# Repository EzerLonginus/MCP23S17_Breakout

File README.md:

# MCP23S17_Breakout
Breakout for MCP23S17

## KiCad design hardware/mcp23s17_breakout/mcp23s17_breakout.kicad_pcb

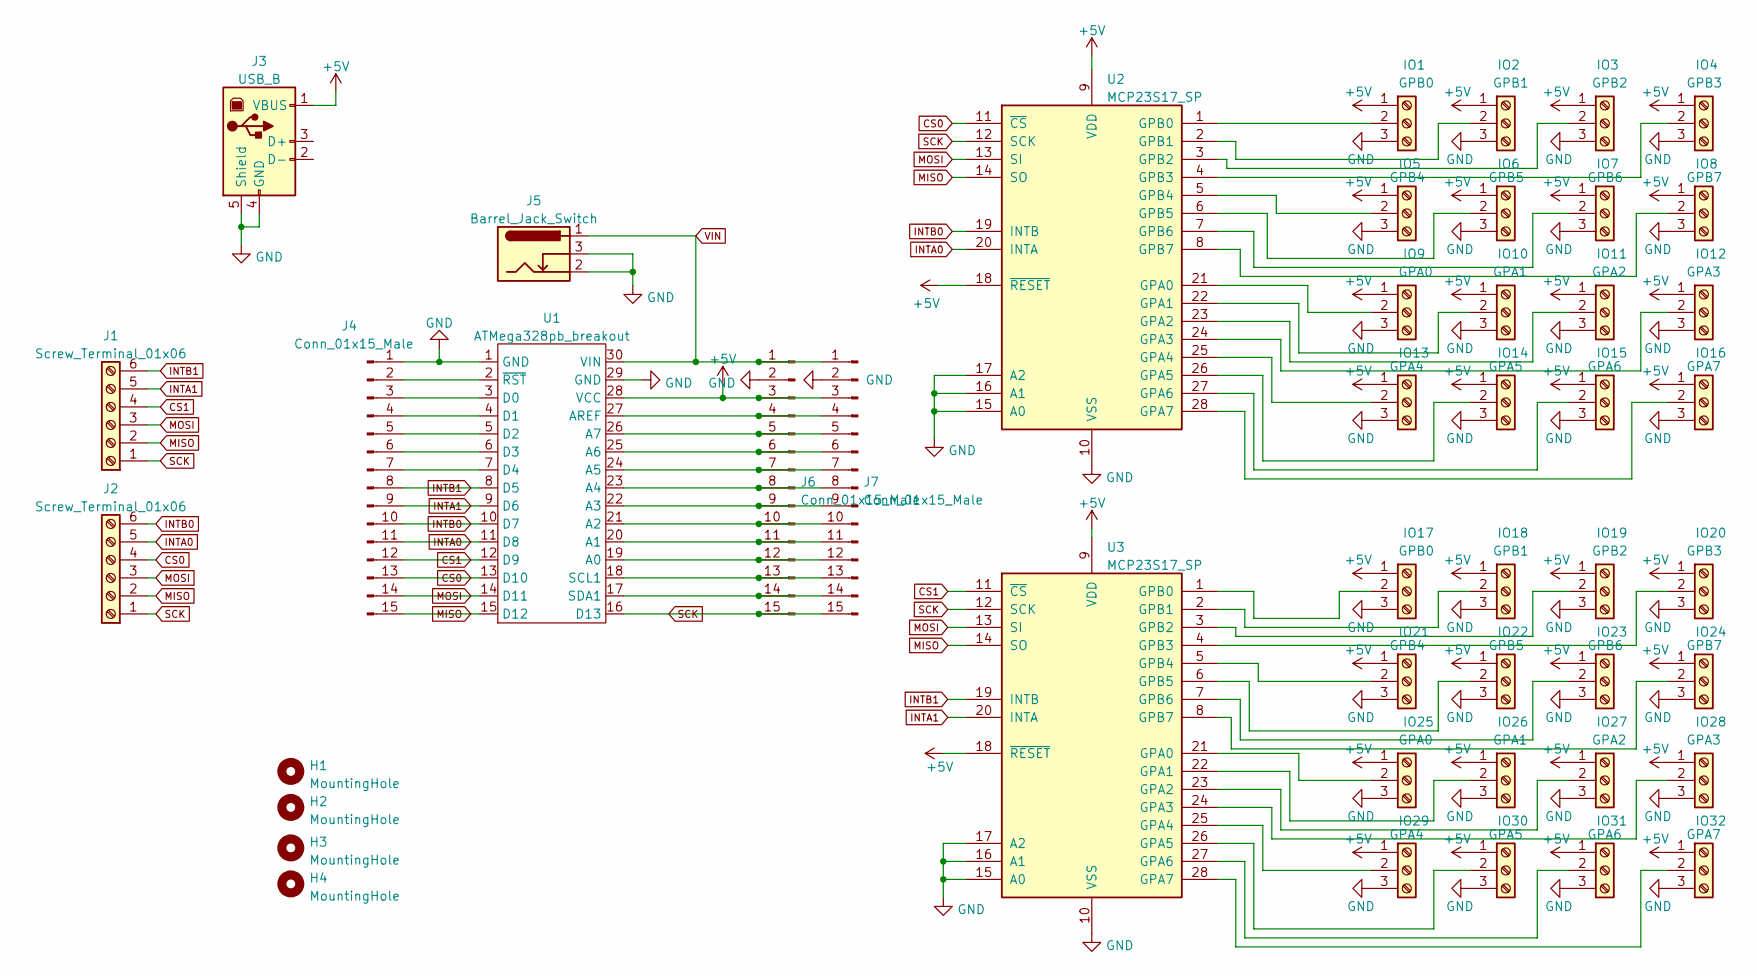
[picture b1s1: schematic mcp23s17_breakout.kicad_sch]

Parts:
H1, H2, H3, H4: MountingHole; MountingHole_3.2mm_M3_DIN965_Pad
IO1, IO17: GPB0; TerminalBlock_TE_282834-3_1x03_P2.54mm_Horizontal
IO2, IO18: GPB1; TerminalBlock_TE_282834-3_1x03_P2.54mm_Horizontal
IO3, IO19: GPB2; TerminalBlock_TE_282834-3_1x03_P2.54mm_Horizontal
IO4, IO20: GPB3; TerminalBlock_TE_282834-3_1x03_P2.54mm_Horizontal
IO5, IO21: GPB4; TerminalBlock_TE_282834-3_1x03_P2.54mm_Horizontal
IO6, IO22: GPB5; TerminalBlock_TE_282834-3_1x03_P2.54mm_Horizontal
IO7, IO23: GPB6; TerminalBlock_TE_282834-3_1x03_P2.54mm_Horizontal
IO8, IO24: GPB7; TerminalBlock_TE_282834-3_1x03_P2.54mm_Horizontal
IO9, IO25: GPA0; TerminalBlock_TE_282834-3_1x03_P2.54mm_Horizontal
IO10, IO26: GPA1; TerminalBlock_TE_282834-3_1x03_P2.54mm_Horizontal
IO11, IO27: GPA2; TerminalBlock_TE_282834-3_1x03_P2.54mm_Horizontal
IO12, IO28: GPA3; TerminalBlock_TE_282834-3_1x03_P2.54mm_Horizontal
IO13, IO29: GPA4; TerminalBlock_TE_282834-3_1x03_P2.54mm_Horizontal
IO14, IO30: GPA5; TerminalBlock_TE_282834-3_1x03_P2.54mm_Horizontal
IO15, IO31: GPA6; TerminalBlock_TE_282834-3_1x03_P2.54mm_Horizontal
IO16, IO32: GPA7; TerminalBlock_TE_282834-3_1x03_P2.54mm_Horizontal
J1, J2: Screw_Terminal_01x06; TerminalBlock_TE_282834-6_1x06_P2.54mm_Horizontal
J3: USB_B; USB_B_Lumberg_2411_02_Horizontal
J4, J6, J7: Conn_01x15_Male; PinHeader_1x15_P2.54mm_Vertical
J5: Barrel_Jack_Switch; BarrelJack_GCT_DCJ200-10-A_Horizontal
U1: ATMega328pb_breakout
U2, U3: MCP23S17_SP; DIP-28_W7.62mm

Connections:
+5V: IO1.1, IO2.1, IO3.1, IO4.1, IO5.1, IO6.1, IO7.1, IO8.1, IO9.1, IO10.1, IO11.1, IO12.1, IO13.1, IO14.1, IO15.1, IO16.1, IO17.1, IO18.1, IO19.1, IO20.1, IO21.1, IO22.1, IO23.1, IO24.1, IO25.1, IO26.1, IO27.1, IO28.1, IO29.1, IO30.1, IO31.1, IO32.1, J3.1 (VBUS), J6.3, J7.3, U1.28 (VCC), U2.9 (VDD), U2.18 (~RESET), U3.9 (VDD), U3.18 (~RESET)
CS0: J2.4, J4.13, U1.13 (D10), U2.11 (~CS)
CS1: J1.4, J4.12, U1.12 (D9), U3.11 (~CS)
GND: IO1.3, IO2.3, IO3.3, IO4.3, IO5.3, IO6.3, IO7.3, IO8.3, IO9.3, IO10.3, IO11.3, IO12.3, IO13.3, IO14.3, IO15.3, IO16.3, IO17.3, IO18.3, IO19.3, IO20.3, IO21.3, IO22.3, IO23.3, IO24.3, IO25.3, IO26.3, IO27.3, IO28.3, IO29.3, IO30.3, IO31.3, IO32.3, J3.4 (GND), J3.5 (Shield), J4.1, J5.2, J5.3, J6.2, J7.2, U1.1 (GND), U1.29 (GND), U2.10 (VSS), U2.15 (A0), U2.16 (A1), U2.17 (A2), U3.10 (VSS), U3.15 (A0), U3.16 (A1), U3.17 (A2)
INTA0: J2.5, J4.11, U1.11 (D8), U2.20 (INTA)
INTA1: J1.5, J4.9, U1.9 (D6), U3.20 (INTA)
INTB0: J2.6, J4.10, U1.10 (D7), U2.19 (INTB)
INTB1: J1.6, J4.8, U1.8 (D5), U3.19 (INTB)
MISO: J1.2, J2.2, J4.15, U1.15 (D12), U2.14 (SO), U3.14 (SO)
MOSI: J1.3, J2.3, J4.14, U1.14 (D11), U2.13 (SI), U3.13 (SI)
unnamed: IO1.2, U2.1 (GPB0)
unnamed: IO2.2, U2.2 (GPB1)
unnamed: IO3.2, U2.3 (GPB2)
unnamed: IO4.2, U2.4 (GPB3)
unnamed: IO5.2, U2.5 (GPB4)
unnamed: IO6.2, U2.6 (GPB5)
unnamed: IO7.2, U2.7 (GPB6)
unnamed: IO8.2, U2.8 (GPB7)
unnamed: IO9.2, U2.21 (GPA0)
unnamed: IO10.2, U2.22 (GPA1)
unnamed: IO11.2, U2.23 (GPA2)
unnamed: IO12.2, U2.24 (GPA3)
unnamed: IO13.2, U2.25 (GPA4)
unnamed: IO14.2, U2.26 (GPA5)
unnamed: IO15.2, U2.27 (GPA6)
unnamed: IO16.2, U2.28 (GPA7)
unnamed: IO17.2, U3.1 (GPB0)
unnamed: IO18.2, U3.2 (GPB1)
unnamed: IO19.2, U3.3 (GPB2)
unnamed: IO20.2, U3.4 (GPB3)
unnamed: IO21.2, U3.5 (GPB4)
unnamed: IO22.2, U3.6 (GPB5)
unnamed: IO23.2, U3.7 (GPB6)
unnamed: IO24.2, U3.8 (GPB7)
unnamed: IO25.2, U3.21 (GPA0)
unnamed: IO26.2, U3.22 (GPA1)
unnamed: IO27.2, U3.23 (GPA2)
unnamed: IO28.2, U3.24 (GPA3)
unnamed: IO29.2, U3.25 (GPA4)
unnamed: IO30.2, U3.26 (GPA5)
unnamed: IO31.2, U3.27 (GPA6)
unnamed: IO32.2, U3.28 (GPA7)
unnamed: J4.2, U1.2 (~RST)
unnamed: J4.3, U1.3 (D0)
unnamed: J4.4, U1.4 (D1)
unnamed: J4.5, U1.5 (D2)
unnamed: J4.6, U1.6 (D3)
unnamed: J4.7, U1.7 (D4)
unnamed: J6.4, J7.4, U1.27 (AREF)
unnamed: J6.5, J7.5, U1.26 (A7)
unnamed: J6.6, J7.6, U1.25 (A6)
unnamed: J6.7, J7.7, U1.24 (A5)
unnamed: J6.8, J7.8, U1.23 (A4)
unnamed: J6.9, J7.9, U1.22 (A3)
unnamed: J6.10, J7.10, U1.21 (A2)
unnamed: J6.11, J7.11, U1.20 (A1)
unnamed: J6.12, J7.12, U1.19 (A0)
unnamed: J6.13, J7.13, U1.18 (SCL1)
unnamed: J6.14, J7.14, U1.17 (SDA1)
SCK: J1.1, J2.1, J6.15, J7.15, U1.16 (D13), U2.12 (SCK), U3.12 (SCK)
VIN: J5.1, J6.1, J7.1, U1.30 (VIN)

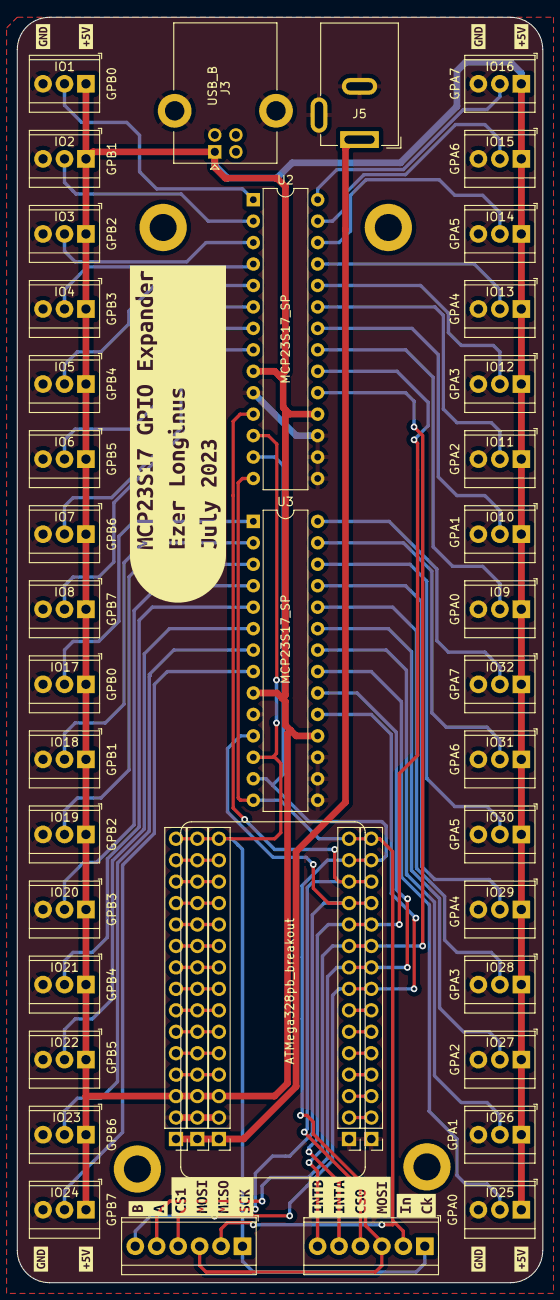
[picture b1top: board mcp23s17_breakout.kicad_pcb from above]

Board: 2 copper layers, 62.2 x 149.9 mm, 59 parts (0 on the bottom side), 61 nets.

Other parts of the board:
kibuzzard-64B054A6, kibuzzard-64B054A6#2, kibuzzard-64B054A6#3: G***; kibuzzard-64B054A6
kibuzzard-64B056E4: G***; kibuzzard-64B056E4
kibuzzard-64B0570E: G***; kibuzzard-64B0570E
kibuzzard-64B0572C: G***; kibuzzard-64B0572C
kibuzzard-64B0577B: G***; kibuzzard-64B0577B
kibuzzard-64B05466: G***; kibuzzard-64B05466
kibuzzard-64B05493, kibuzzard-64B05493#2, kibuzzard-64B05493#3, kibuzzard-64B05493#4: G***; kibuzzard-64B05493
kibuzzard-64B05998: G***; kibuzzard-64B05998

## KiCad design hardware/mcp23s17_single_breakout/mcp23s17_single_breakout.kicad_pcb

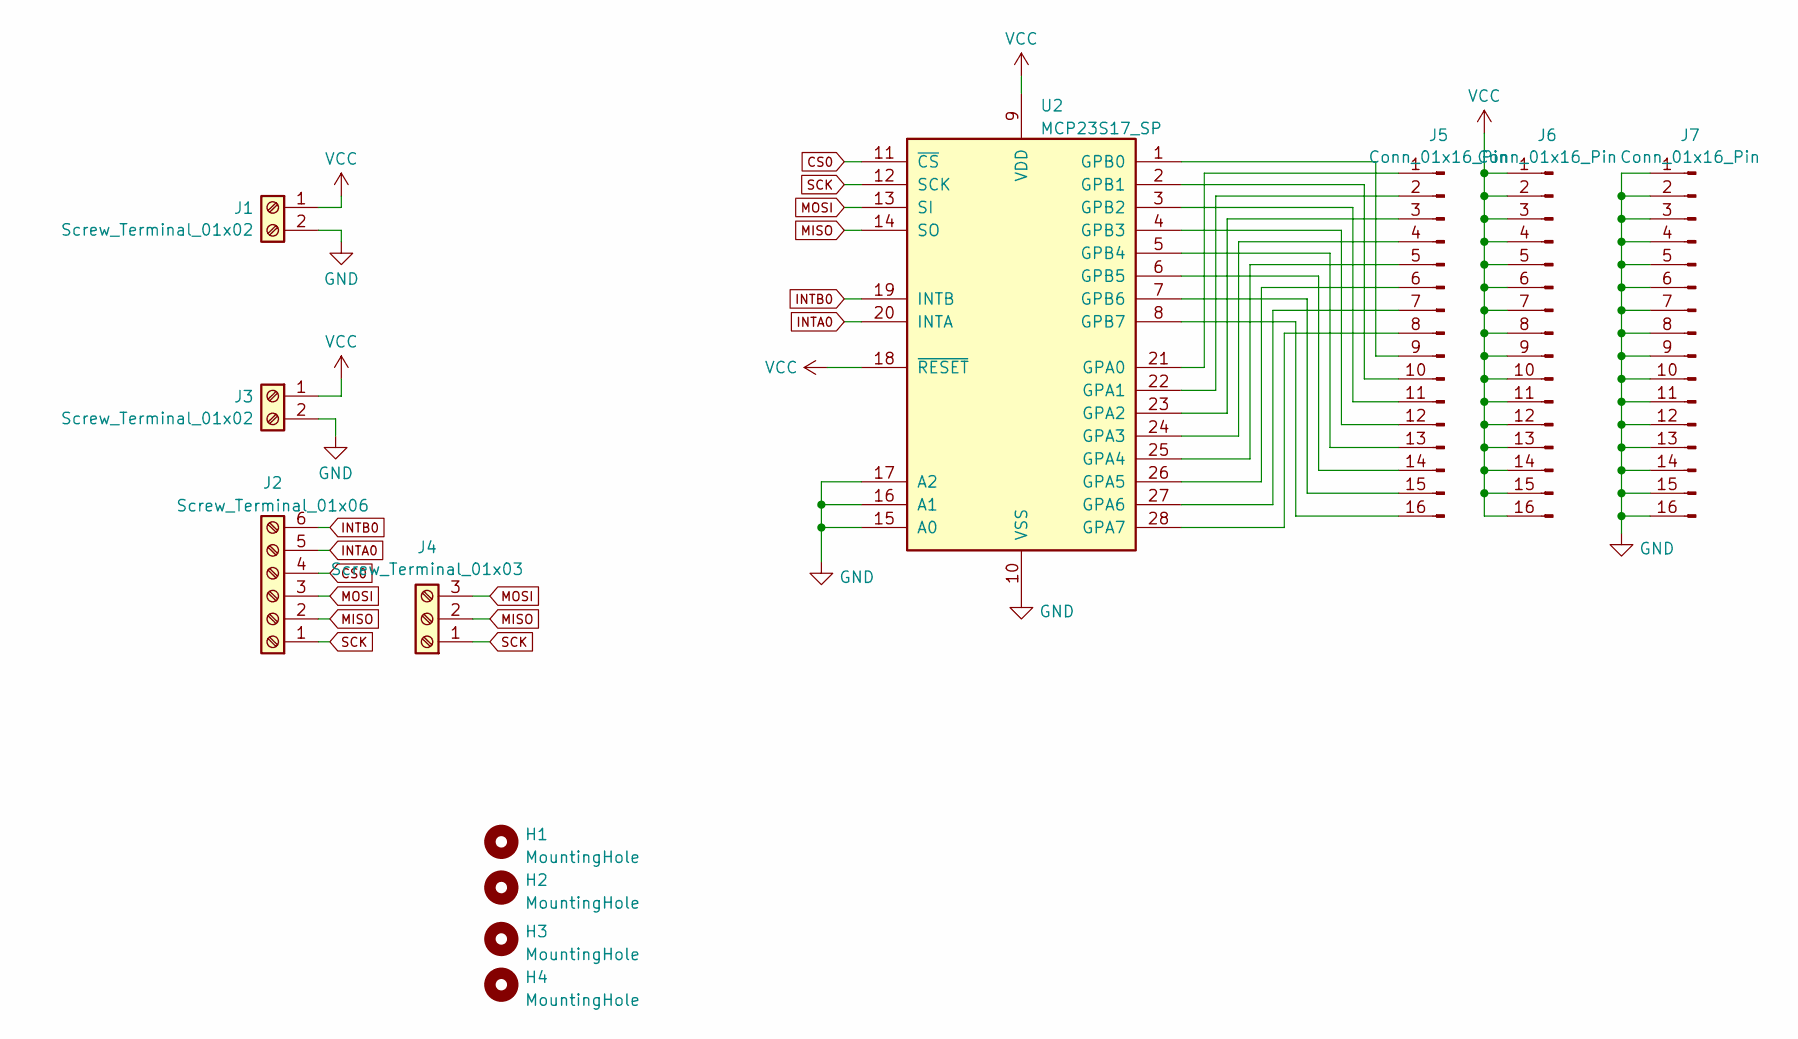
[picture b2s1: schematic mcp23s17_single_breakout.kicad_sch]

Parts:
H1, H2, H3, H4: MountingHole; MountingHole_3.2mm_M3_DIN965_Pad
J1, J3: Screw_Terminal_01x02; TerminalBlock_bornier-2_P5.08mm
J2: Screw_Terminal_01x06; TerminalBlock_4Ucon_1x06_P3.50mm_Horizontal
J4: Screw_Terminal_01x03; TerminalBlock_4Ucon_1x03_P3.50mm_Horizontal
J5, J6, J7: Conn_01x16_Pin; PinHeader_1x16_P2.54mm_Vertical
U2: MCP23S17_SP; DIP-28_W7.62mm

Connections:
CS0: J2.4, U2.11 (~CS)
GND: J1.2, J3.2, J7.1, J7.2, J7.3, J7.4, J7.5, J7.6, J7.7, J7.8, J7.9, J7.10, J7.11, J7.12, J7.13, J7.14, J7.15, J7.16, U2.10 (VSS), U2.15 (A0), U2.16 (A1), U2.17 (A2)
INTA0: J2.5, U2.20 (INTA)
INTB0: J2.6, U2.19 (INTB)
MISO: J2.2, J4.2, U2.14 (SO)
MOSI: J2.3, J4.3, U2.13 (SI)
unnamed: J5.1, U2.21 (GPA0)
unnamed: J5.2, U2.22 (GPA1)
unnamed: J5.3, U2.23 (GPA2)
unnamed: J5.4, U2.24 (GPA3)
unnamed: J5.5, U2.25 (GPA4)
unnamed: J5.6, U2.26 (GPA5)
unnamed: J5.7, U2.27 (GPA6)
unnamed: J5.8, U2.28 (GPA7)
unnamed: J5.9, U2.1 (GPB0)
unnamed: J5.10, U2.2 (GPB1)
unnamed: J5.11, U2.3 (GPB2)
unnamed: J5.12, U2.4 (GPB3)
unnamed: J5.13, U2.5 (GPB4)
unnamed: J5.14, U2.6 (GPB5)
unnamed: J5.15, U2.7 (GPB6)
unnamed: J5.16, U2.8 (GPB7)
SCK: J2.1, J4.1, U2.12 (SCK)
VCC: J1.1, J3.1, J6.1, J6.2, J6.3, J6.4, J6.5, J6.6, J6.7, J6.8, J6.9, J6.10, J6.11, J6.12, J6.13, J6.14, J6.15, J6.16, U2.9 (VDD), U2.18 (~RESET)

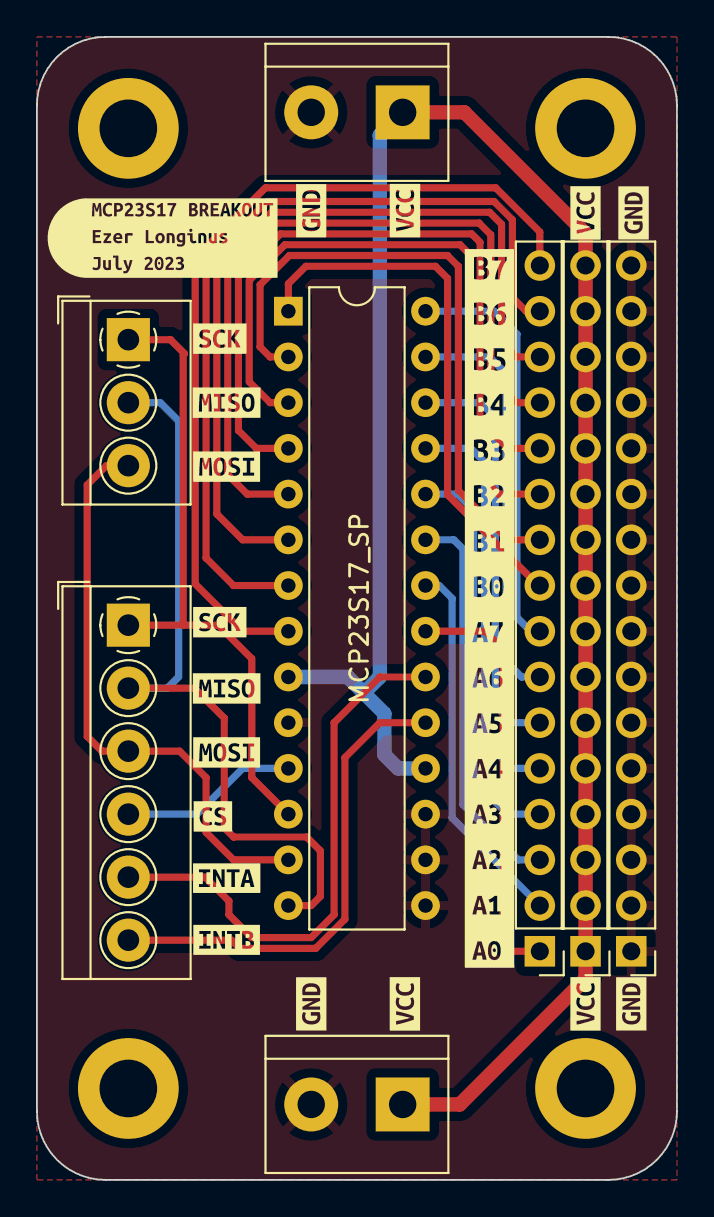
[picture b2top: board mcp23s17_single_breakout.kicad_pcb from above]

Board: 2 copper layers, 35.6 x 63.5 mm, 31 parts (0 on the bottom side), 24 nets.

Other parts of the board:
kibuzzard-64B17B8E, kibuzzard-64B17B8E#2: G***; kibuzzard-64B17B8E
kibuzzard-64B17BBB, kibuzzard-64B17BBB#2: G***; kibuzzard-64B17BBB
kibuzzard-64B17BDD, kibuzzard-64B17BDD#2: G***; kibuzzard-64B17BDD
kibuzzard-64B17C16: G***; kibuzzard-64B17C16
kibuzzard-64B17C26: G***; kibuzzard-64B17C26
kibuzzard-64B17C33: G***; kibuzzard-64B17C33
kibuzzard-64B17C58, kibuzzard-64B17C58#2, kibuzzard-64B17C58#3, kibuzzard-64B17C58#4: G***; kibuzzard-64B17C58
kibuzzard-64B17C80, kibuzzard-64B17C80#2, kibuzzard-64B17C80#3, kibuzzard-64B17C80#4: G***; kibuzzard-64B17C80
kibuzzard-64B17E8C: G***; kibuzzard-64B17E8C
kibuzzard-64B56916: G***; kibuzzard-64B56916

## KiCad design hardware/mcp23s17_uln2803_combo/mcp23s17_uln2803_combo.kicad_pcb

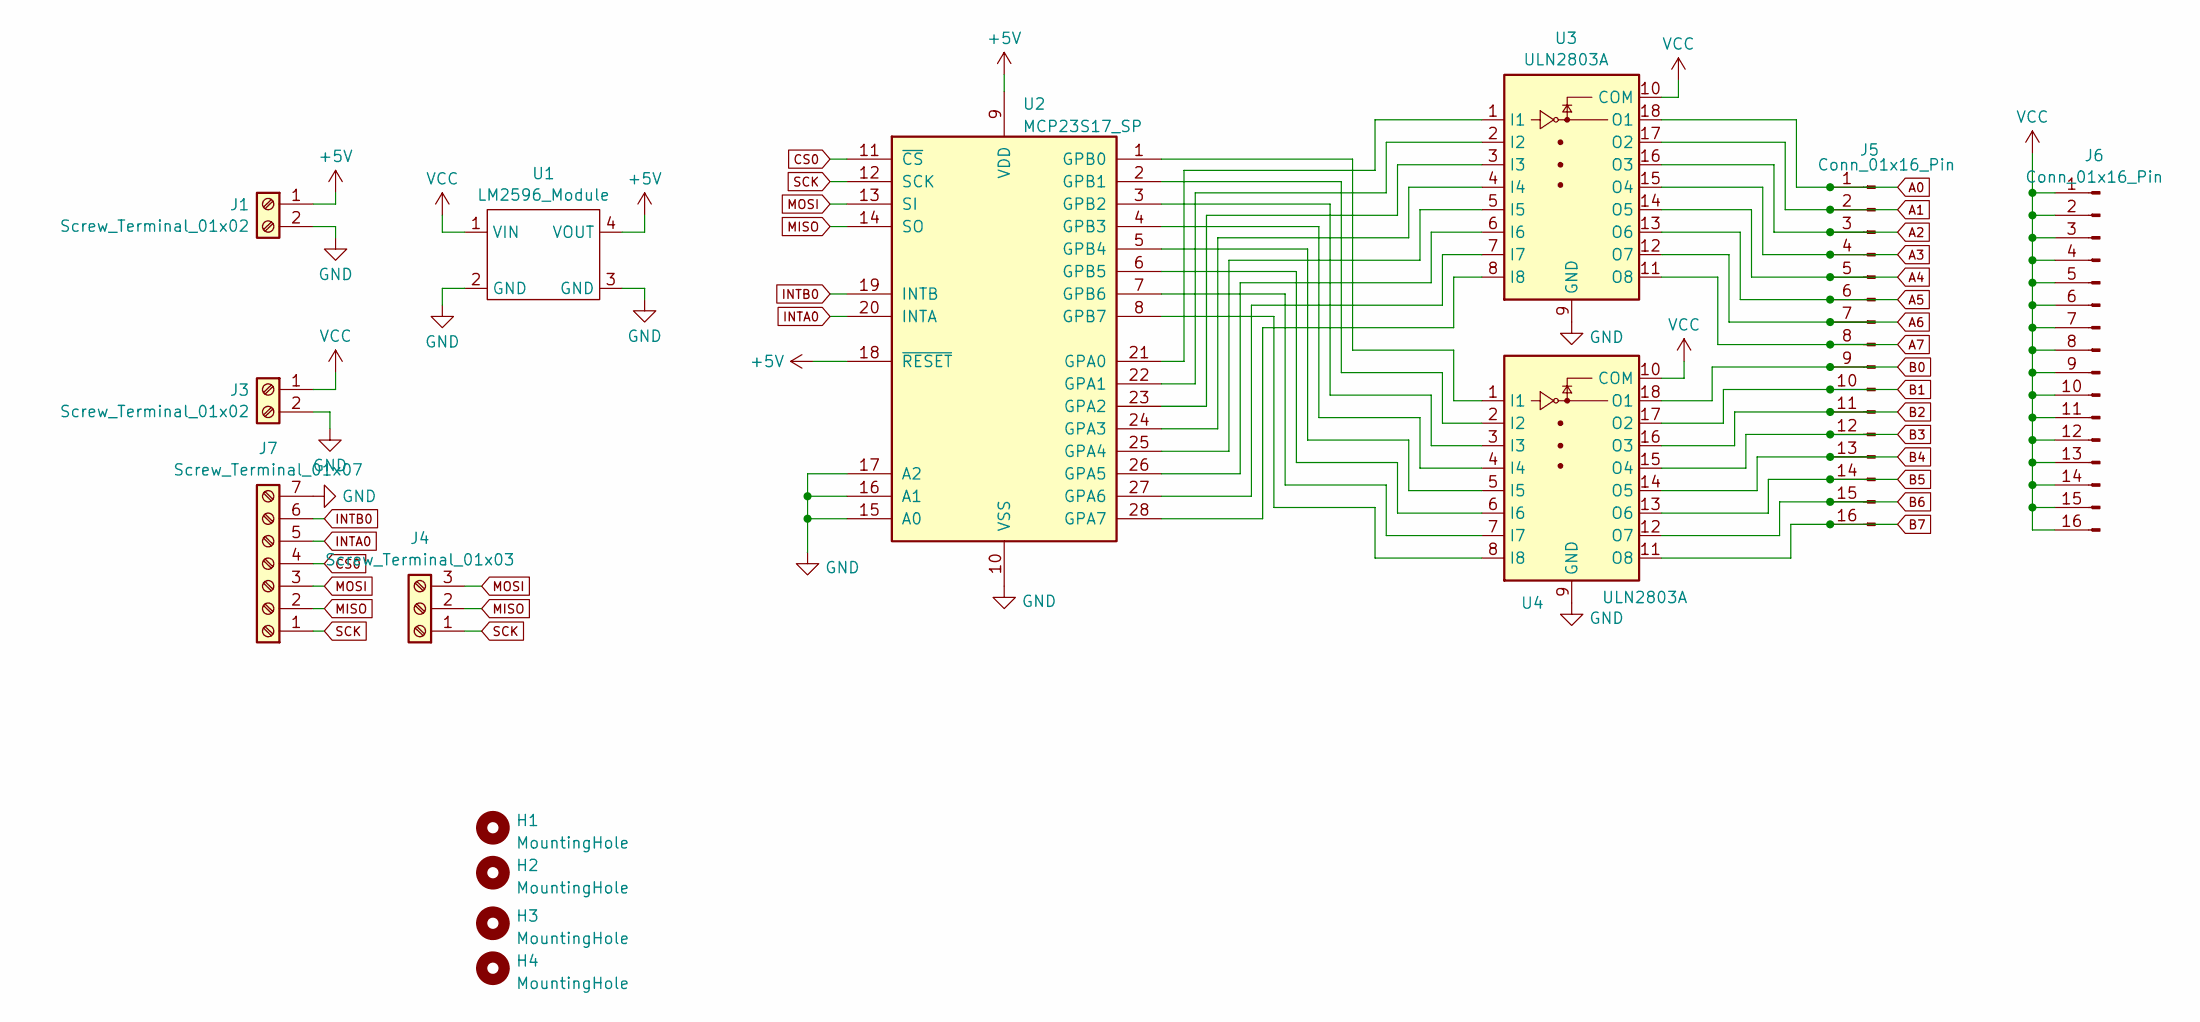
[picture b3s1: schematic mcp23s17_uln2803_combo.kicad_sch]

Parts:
H1, H2, H3, H4: MountingHole; MountingHole_3.2mm_M3_DIN965_Pad
J1, J3: Screw_Terminal_01x02; TerminalBlock_bornier-2_P5.08mm
J4: Screw_Terminal_01x03; TerminalBlock_4Ucon_1x03_P3.50mm_Horizontal
J5, J6: Conn_01x16_Pin; PinHeader_1x16_P2.54mm_Vertical
J7: Screw_Terminal_01x07; TerminalBlock_4Ucon_1x07_P3.50mm_Horizontal
U1: LM2596_Module; LM2596_StepDown_Module
U2: MCP23S17_SP; DIP-28_W7.62mm
U3, U4: ULN2803A; DIP-18_W7.62mm_LongPads

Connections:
+5V: J1.1, U1.4 (VOUT), U2.9 (VDD), U2.18 (~RESET)
A0: J5.1, U3.18 (O1)
A1: J5.2, U3.17 (O2)
A2: J5.3, U3.16 (O3)
A3: J5.4, U3.15 (O4)
A4: J5.5, U3.14 (O5)
A5: J5.6, U3.13 (O6)
A6: J5.7, U3.12 (O7)
A7: J5.8, U3.11 (O8)
B0: J5.9, U4.18 (O1)
B1: J5.10, U4.17 (O2)
B2: J5.11, U4.16 (O3)
B3: J5.12, U4.15 (O4)
B4: J5.13, U4.14 (O5)
B5: J5.14, U4.13 (O6)
B6: J5.15, U4.12 (O7)
B7: J5.16, U4.11 (O8)
CS0: J7.4, U2.11 (~CS)
GND: J1.2, J3.2, J7.7, U1.2 (GND), U1.3 (GND), U2.10 (VSS), U2.15 (A0), U2.16 (A1), U2.17 (A2), U3.9 (GND), U4.9 (GND)
INTA0: J7.5, U2.20 (INTA)
INTB0: J7.6, U2.19 (INTB)
MISO: J4.2, J7.2, U2.14 (SO)
MOSI: J4.3, J7.3, U2.13 (SI)
unnamed: U2.21 (GPA0), U3.1 (I1)
unnamed: U2.22 (GPA1), U3.2 (I2)
unnamed: U2.23 (GPA2), U3.3 (I3)
unnamed: U2.24 (GPA3), U3.4 (I4)
unnamed: U2.25 (GPA4), U3.5 (I5)
unnamed: U2.26 (GPA5), U3.6 (I6)
unnamed: U2.27 (GPA6), U3.7 (I7)
unnamed: U2.28 (GPA7), U3.8 (I8)
unnamed: U2.1 (GPB0), U4.1 (I1)
unnamed: U2.2 (GPB1), U4.2 (I2)
unnamed: U2.3 (GPB2), U4.3 (I3)
unnamed: U2.4 (GPB3), U4.4 (I4)
unnamed: U2.5 (GPB4), U4.5 (I5)
unnamed: U2.6 (GPB5), U4.6 (I6)
unnamed: U2.7 (GPB6), U4.7 (I7)
unnamed: U2.8 (GPB7), U4.8 (I8)
SCK: J4.1, J7.1, U2.12 (SCK)
VCC: J3.1, J6.1, J6.2, J6.3, J6.4, J6.5, J6.6, J6.7, J6.8, J6.9, J6.10, J6.11, J6.12, J6.13, J6.14, J6.15, J6.16, U1.1 (VIN), U3.10 (COM), U4.10 (COM)

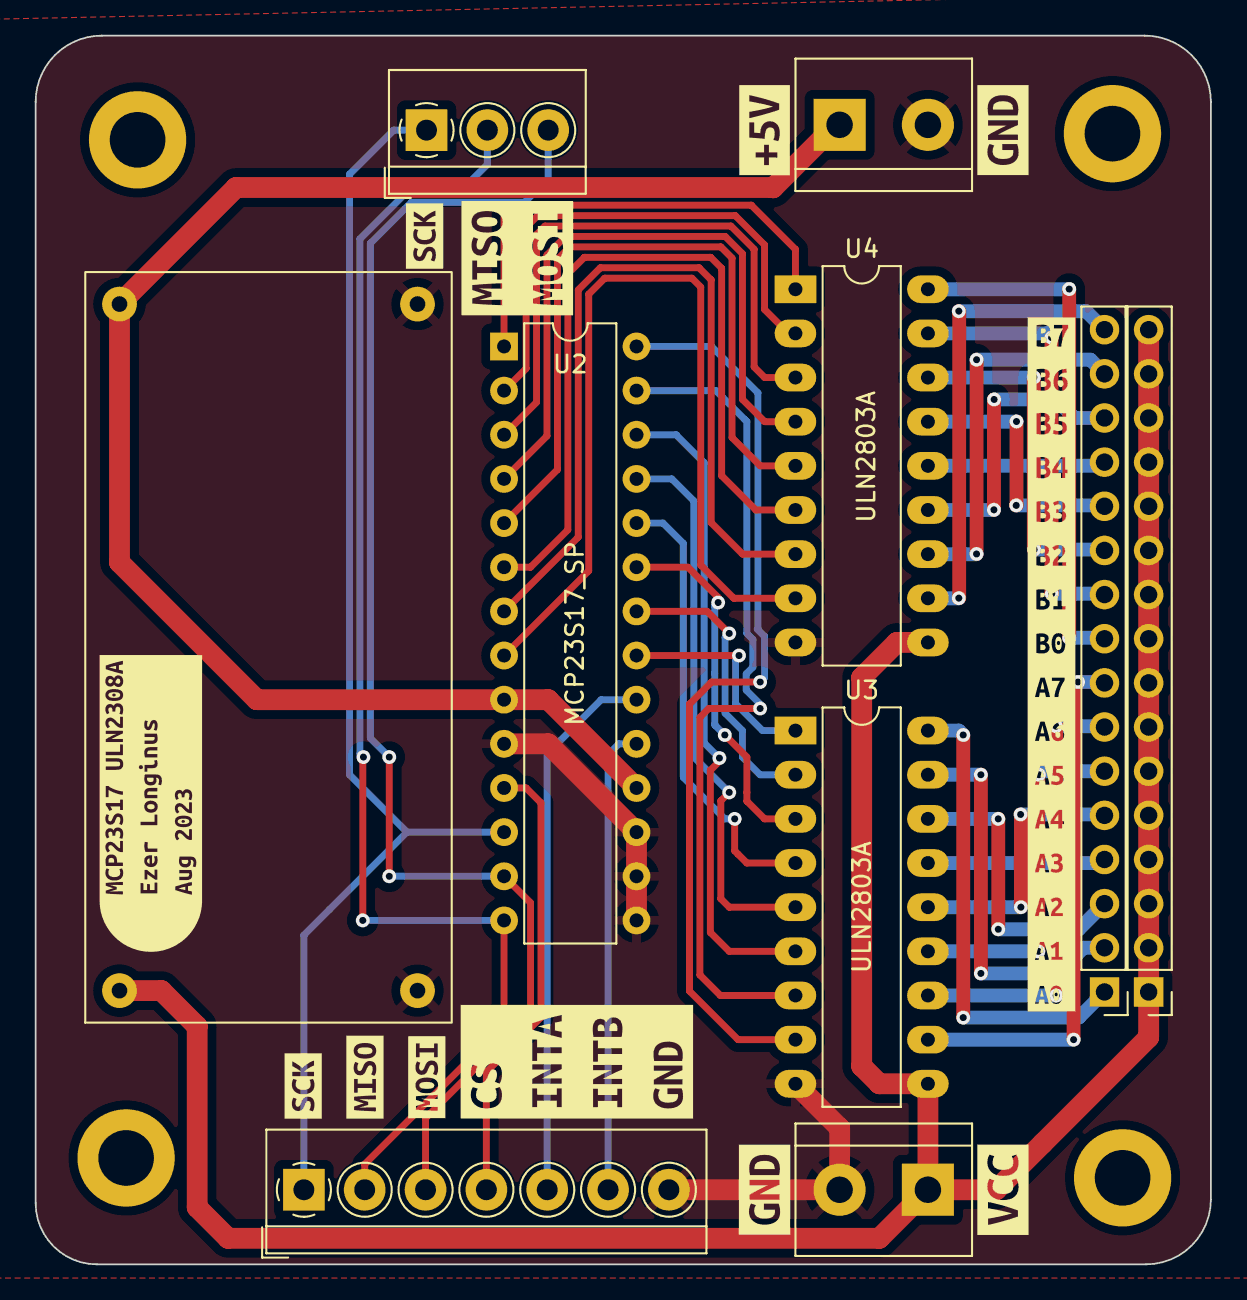
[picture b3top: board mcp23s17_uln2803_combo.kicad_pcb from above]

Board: 2 copper layers, 67.6 x 70.7 mm, 26 parts (0 on the bottom side), 41 nets.

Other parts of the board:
kibuzzard-64B56A6B: G***; kibuzzard-64B56A6B
kibuzzard-64B56A53: G***; kibuzzard-64B56A53
kibuzzard-64B56A86: G***; kibuzzard-64B56A86
kibuzzard-64B56A95: G***; kibuzzard-64B56A95
kibuzzard-64B56ACB: G***; kibuzzard-64B56ACB
kibuzzard-64B56AD8: G***; kibuzzard-64B56AD8
kibuzzard-64B580B5: G***; kibuzzard-64B580B5
kibuzzard-64B580D1: G***; kibuzzard-64B580D1
kibuzzard-64B56972: G***; kibuzzard-64B56972
kibuzzard-64C9511E: G***; kibuzzard-64C9511E
kibuzzard-64C95159: G***; kibuzzard-64C95159
kibuzzard-64CC0265: G***; kibuzzard-64CC0265

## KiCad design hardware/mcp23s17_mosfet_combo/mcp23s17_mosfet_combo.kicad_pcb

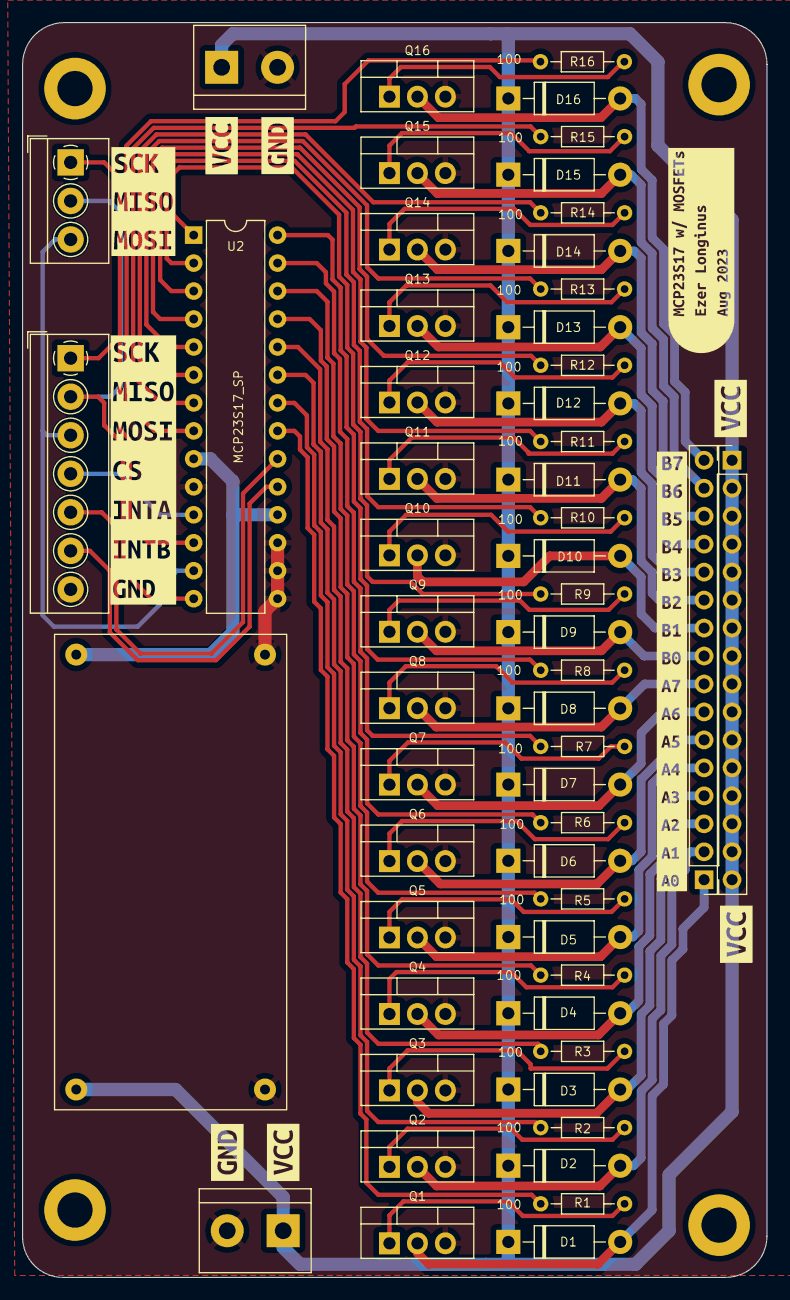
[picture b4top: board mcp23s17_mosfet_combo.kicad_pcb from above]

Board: 2 copper layers, 67.6 x 114.0 mm, 70 parts (0 on the bottom side), 57 nets.

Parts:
D1, D2, D3, D4, D5, D6, D7, D8, D9, D10, D11, D12, D13, D14, D15, D16: 1N4004; D_DO-41_SOD81_P10.16mm_Horizontal
H1, H2, H3, H4: MountingHole; MountingHole_3.2mm_M3_DIN965_Pad
J1, J3: Screw_Terminal_01x02; TerminalBlock_bornier-2_P5.08mm
J4: Screw_Terminal_01x03; TerminalBlock_4Ucon_1x03_P3.50mm_Horizontal
J5, J6: Conn_01x16_Pin; PinHeader_1x16_P2.54mm_Vertical
J7: Screw_Terminal_01x07; TerminalBlock_4Ucon_1x07_P3.50mm_Horizontal
Q1, Q2, Q3, Q4, Q5, Q6, Q7, Q8, Q9, Q10, Q11, Q12, Q13, Q14, Q15, Q16: IPP060N06N; TO-220-3_Vertical
R1, R2, R3, R4, R5, R6, R7, R8, R9, R10, R11, R12, R13, R14, R15, R16: 100; R_Axial_DIN0204_L3.6mm_D1.6mm_P7.62mm_Horizontal
U1: LM2596_Module; LM2596_StepDown_Module
U2: MCP23S17_SP; DIP-28_W7.62mm
kibuzzard-64B56A95: G***; kibuzzard-64B56A95
kibuzzard-64B56ACB: G***; kibuzzard-64B56ACB
kibuzzard-64B56AD8: G***; kibuzzard-64B56AD8
kibuzzard-64CBF5AA: G***; kibuzzard-64CBF5AA
kibuzzard-64CBF5CE, kibuzzard-64CBF5CE#2, kibuzzard-64CBF5CE#3: G***; kibuzzard-64CBF5CE
kibuzzard-64CBF6A4: G***; kibuzzard-64CBF6A4
kibuzzard-64CBF66B: G***; kibuzzard-64CBF66B
kibuzzard-64CBFA42: G***; kibuzzard-64CBFA42

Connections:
+5V: U1.4 (VOUT), U2.9 (VDD), U2.18 (~RESET)
/MOSFETS/IN_A0: R1.1, U2.21 (GPA0)
/MOSFETS/IN_A1: R2.1, U2.22 (GPA1)
/MOSFETS/IN_A2: R3.1, U2.23 (GPA2)
/MOSFETS/IN_A3: R4.1, U2.24 (GPA3)
/MOSFETS/IN_A4: R5.1, U2.25 (GPA4)
/MOSFETS/IN_A5: R6.1, U2.26 (GPA5)
/MOSFETS/IN_A6: R7.1, U2.27 (GPA6)
/MOSFETS/IN_A7: R8.1, U2.28 (GPA7)
/MOSFETS/IN_B0: R9.1, U2.1 (GPB0)
/MOSFETS/IN_B1: R10.1, U2.2 (GPB1)
/MOSFETS/IN_B2: R11.1, U2.3 (GPB2)
/MOSFETS/IN_B3: R12.1, U2.4 (GPB3)
/MOSFETS/IN_B4: R13.1, U2.5 (GPB4)
/MOSFETS/IN_B5: R14.1, U2.6 (GPB5)
/MOSFETS/IN_B6: R15.1, U2.7 (GPB6)
/MOSFETS/IN_B7: R16.1, U2.8 (GPB7)
A0: D1.2 (A), J5.1, Q1.2 (D)
A1: D2.2 (A), J5.2, Q2.2 (D)
A2: D3.2 (A), J5.3, Q3.2 (D)
A3: D4.2 (A), J5.4, Q4.2 (D)
A4: D5.2 (A), J5.5, Q5.2 (D)
A5: D6.2 (A), J5.6, Q6.2 (D)
A6: D7.2 (A), J5.7, Q7.2 (D)
A7: D8.2 (A), J5.8, Q8.2 (D)
B0: D9.2 (A), J5.9, Q9.2 (D)
B1: D10.2 (A), J5.10, Q10.2 (D)
B2: D11.2 (A), J5.11, Q11.2 (D)
B3: D12.2 (A), J5.12, Q12.2 (D)
B4: D13.2 (A), J5.13, Q13.2 (D)
B5: D14.2 (A), J5.14, Q14.2 (D)
B6: D15.2 (A), J5.15, Q15.2 (D)
B7: D16.2 (A), J5.16, Q16.2 (D)
CS0: J7.4, U2.11 (~CS)
GND: J1.2, J3.2, J7.7, Q1.3 (S), Q2.3 (S), Q3.3 (S), Q4.3 (S), Q5.3 (S), Q6.3 (S), Q7.3 (S), Q8.3 (S), Q9.3 (S), Q10.3 (S), Q11.3 (S), Q12.3 (S), Q13.3 (S), Q14.3 (S), Q15.3 (S), Q16.3 (S), U1.2 (GND), U1.3 (GND), U2.10 (VSS), U2.15 (A0), U2.16 (A1), U2.17 (A2)
INTA0: J7.5, U2.20 (INTA)
INTB0: J7.6, U2.19 (INTB)
MISO: J4.2, J7.2, U2.14 (SO)
MOSI: J4.3, J7.3, U2.13 (SI)
unnamed: Q1.1 (G), R1.2
unnamed: Q2.1 (G), R2.2
unnamed: Q3.1 (G), R3.2
unnamed: Q4.1 (G), R4.2
unnamed: Q5.1 (G), R5.2
unnamed: Q6.1 (G), R6.2
unnamed: Q7.1 (G), R7.2
unnamed: Q8.1 (G), R8.2
unnamed: Q9.1 (G), R9.2
unnamed: Q10.1 (G), R10.2
unnamed: Q11.1 (G), R11.2
unnamed: Q12.1 (G), R12.2
unnamed: Q13.1 (G), R13.2
unnamed: Q14.1 (G), R14.2
unnamed: Q15.1 (G), R15.2
unnamed: Q16.1 (G), R16.2
SCK: J4.1, J7.1, U2.12 (SCK)
VCC: D1.1 (K), D2.1 (K), D3.1 (K), D4.1 (K), D5.1 (K), D6.1 (K), D7.1 (K), D8.1 (K), D9.1 (K), D10.1 (K), D11.1 (K), D12.1 (K), D13.1 (K), D14.1 (K), D15.1 (K), D16.1 (K), J1.1, J3.1, J6.1, J6.2, J6.3, J6.4, J6.5, J6.6, J6.7, J6.8, J6.9, J6.10, J6.11, J6.12, J6.13, J6.14, J6.15, J6.16, U1.1 (VIN)

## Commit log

2023-08-10 Initial Board Commit
